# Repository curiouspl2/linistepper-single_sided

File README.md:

# linistepper-single_sided
my version of linistepper board

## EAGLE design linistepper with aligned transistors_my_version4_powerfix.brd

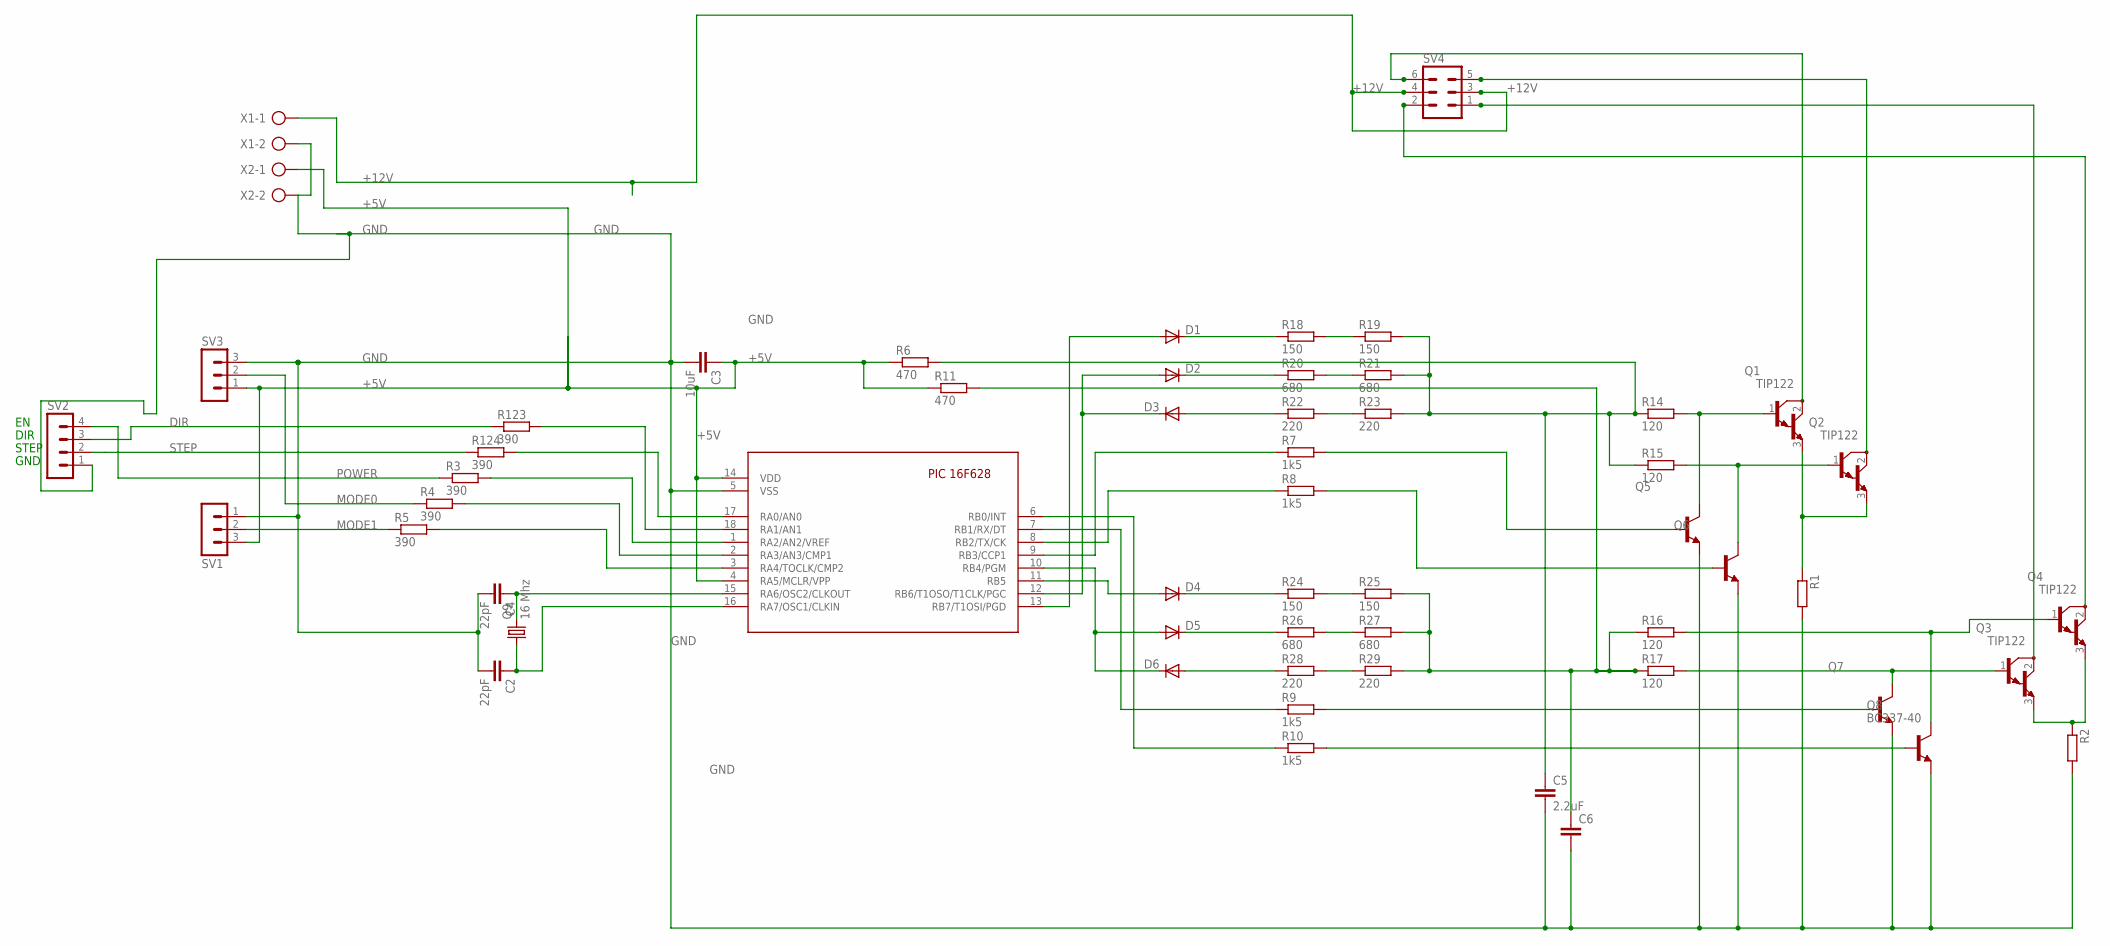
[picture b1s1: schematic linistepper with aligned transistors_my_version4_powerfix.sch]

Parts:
C2, C4: 22pF; C025-024X044
C3: 10uF; C025-040X050
C5: 2.2uF; C050-024X044
C6: C-EU050-024X044; C050-024X044
D1, D2, D3, D4, D5, D6: 1N4148; DO35-10
Q1, Q2, Q3, Q4: TIP122; TO220
Q5, Q6, Q7, Q8: BC337-40; TO92
Q9: 16 Mhz; HC49/S
R1, R2: R-EU_0922/22; 0922/22
R3, R123, R124: 390; 0207/2V
R4: 390; 0411V
R5: 390; 0207/5V
R6: 470; 0207/10
R7: 1k5; 0207/10
R8: 1k5; 0207/7
R9, R10: 1k5; 0207/5V
R11: 470; 0207/7
R14: 120; 0207/10
R15: 120; 0207/7
R16, R17: 120; 0207/5V
R18, R19, R24, R25: 150; 0207/2V
R20, R21, R26, R27: 680; 0207/2V
R22, R23, R28, R29: 220; 0207/2V
SV1, SV3: MA03-1
SV2: MA04-1
SV4: MA03-2
U$1: 16F628; PIC16F628-18-LEAD-PDIP
X1, X2: AK300/2

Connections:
+5V: C3.1, R6.1, R11.1, SV1.3, SV3.1, U$1.4 (RA5/MCLR/VPP), U$1.14 (VDD), X2.1
+12V: SV4.3, SV4.4, X1.1
DIR: R123.1, SV2.3
GND: C2.2, C3.2, C4.2, C5.2, C6.2, Q5.1 (E), Q6.1 (E), Q7.1 (E), Q8.1 (E), R1.2, R2.2, SV1.1, SV2.1, SV3.3, U$1.5 (VSS), X1.2, X2.2
MODE0: R4.1, SV3.2
MODE1: R5.1, SV1.2
unnamed: R18.2, R19.1
unnamed: C5.1, R6.2, R14.1, R15.1, R19.2, R21.2, R23.2
unnamed: R20.2, R21.1
unnamed: Q1.1 (B), Q5.3 (C), R14.2
unnamed: Q2.1 (B), Q6.3 (C), R15.2
unnamed: D1.C, R18.1
unnamed: D2.C, R20.1
unnamed: D3.A, R22.1
unnamed: D1.A, U$1.13 (RB7/T1OSI/PGD)
unnamed: D2.A, D3.C, U$1.12 (RB6/T1OSO/T1CLK/PGC)
unnamed: R8.1, U$1.8 (RB2/TX/CK)
unnamed: R7.1, U$1.9 (RB3/CCP1)
unnamed: Q5.2 (B), R7.2
unnamed: Q6.2 (B), R8.2
unnamed: Q1.3 (E), Q2.3 (E), R1.1
unnamed: R3.2, U$1.1 (RA2/AN2/VREF)
unnamed: R4.2, U$1.2 (RA3/AN3/CMP1)
unnamed: R24.2, R25.1
unnamed: D5.C, R26.1
unnamed: R26.2, R27.1
unnamed: D6.A, R28.1
unnamed: R28.2, R29.1
unnamed: D4.A, U$1.11 (RB5)
unnamed: D5.A, D6.C, U$1.10 (RB4/PGM)
unnamed: R9.1, U$1.7 (RB1/RX/DT)
unnamed: R10.1, U$1.6 (RB0/INT)
unnamed: C6.1, R11.2, R16.1, R17.1, R25.2, R27.2, R29.2
unnamed: Q4.1 (B), Q8.3 (C), R16.2
unnamed: Q8.2 (B), R10.2
unnamed: Q3.1 (B), Q7.3 (C), R17.2
unnamed: Q7.2 (B), R9.2
unnamed: Q3.3 (E), Q4.3 (E), R2.1
unnamed: Q1.2 (C), SV4.6
unnamed: Q2.2 (C), SV4.5
unnamed: Q3.2 (C), SV4.1
unnamed: Q4.2 (C), SV4.2
unnamed: R124.2, U$1.17 (RA0/AN0)
unnamed: R123.2, U$1.18 (RA1/AN1)
unnamed: C2.1, Q9.1, U$1.16 (RA7/OSC1/CLKIN)
unnamed: C4.1, Q9.2, U$1.15 (RA6/OSC2/CLKOUT)
unnamed: R5.2, U$1.3 (RA4/TOCLK/CMP2)
POWER: R3.1, SV2.4
R23: R22.2, R23.1
R24: D4.C, R24.1
STEP: R124.1, SV2.2

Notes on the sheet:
STEP
DIR
GND

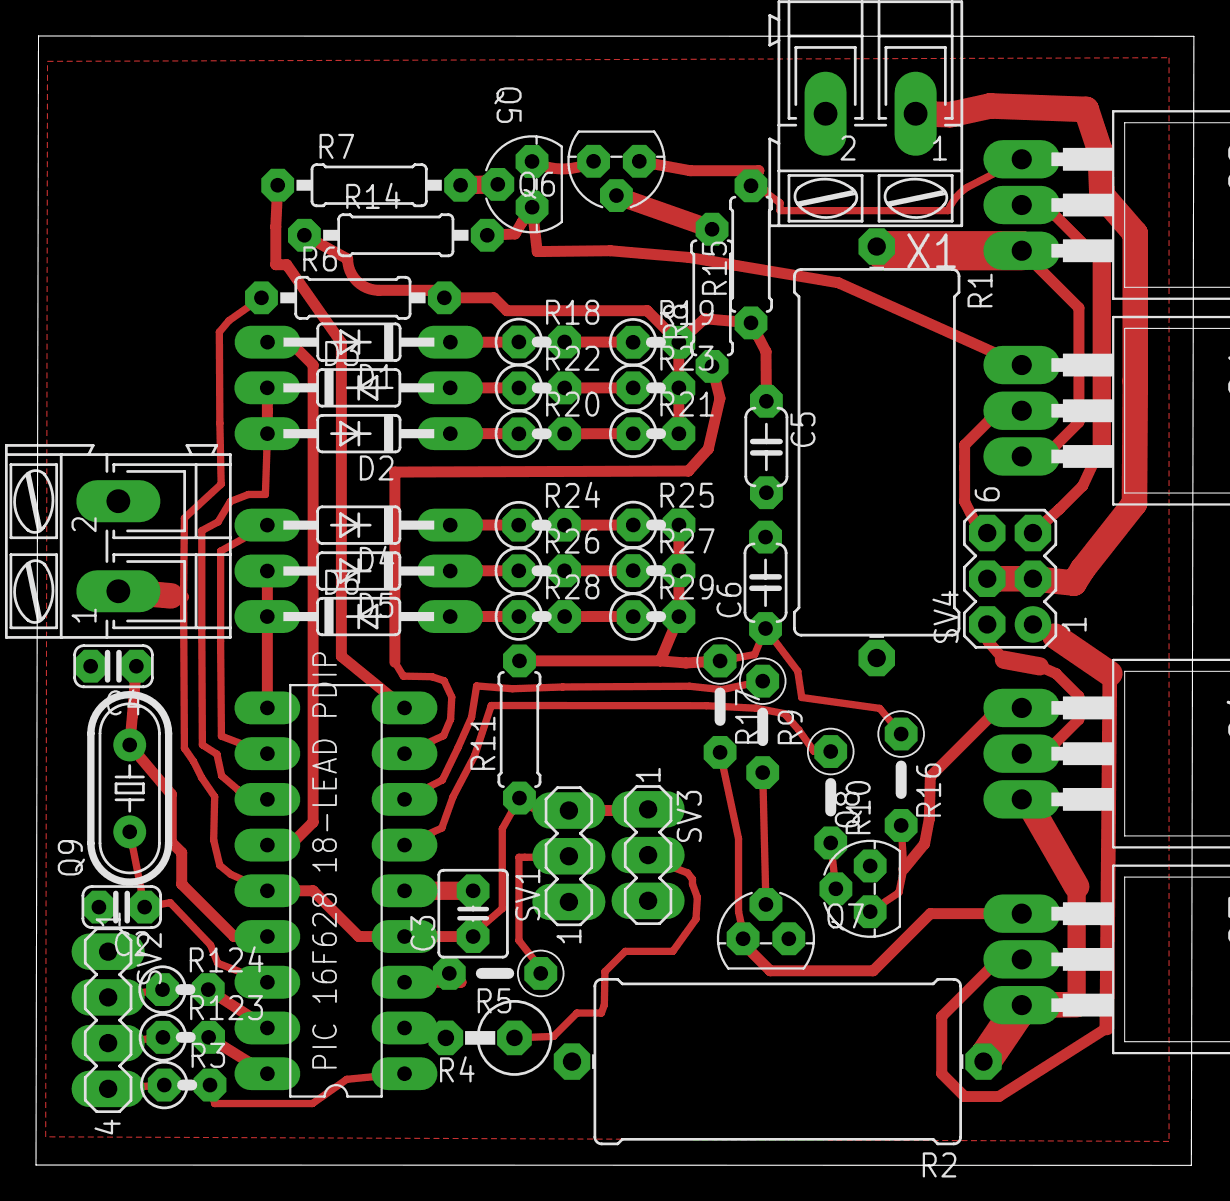
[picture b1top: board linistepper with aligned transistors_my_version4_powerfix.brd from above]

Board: 2 copper layers, 64.3 x 62.7 mm, 56 parts (0 on the bottom side), 51 nets.
